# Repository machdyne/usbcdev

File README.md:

# USBCDEV Pmod™ Compatible Module

This is a simple USB-C module for developing certain USB-C devices directly in FPGA gateware. Note that it’s not possible to precisely meet the USB specs with this PMOD but it might be close enough for your purposes, please check the schematics and layout.

This repo contains PCB layouts, schematics and pinouts.

Find more information on the [product page](https://machdyne.com/product/usbcdev-pmod/).

## Pinout

| Pin | Signal |
| --- | ------ |
| 1 | USB\_DP |
| 2 | USB\_DN |
| 3 | USB\_DP\_PU |
| 4 | USB\_DN\_PU |
| 5 | GND |
| 6 | 3V3 |

## License

The contents of this repo are released under the [Lone Dynamics Open License](LICENSE.md) with the following exceptions:

- The KiCad design files contain parts of the [kicad-pmod](https://github.com/mithro/kicad-pmod) library which is released under the [Apache License, Version 2.0](https://www.apache.org/licenses/LICENSE-2.0.html).

- The KiCad design files may contain symbols and footprints released under other licenses; please contact us if we've failed to give proper attribution.

Note: You can use these designs for commercial purposes but we ask that instead of producing exact clones, that you either replace our trademarks and logos with your own or add your own next to ours.

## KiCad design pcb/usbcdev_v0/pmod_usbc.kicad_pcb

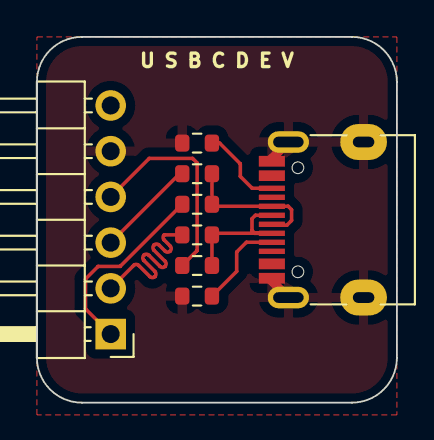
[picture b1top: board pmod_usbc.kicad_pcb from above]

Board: 2 copper layers, 20.0 x 20.3 mm, 8 parts (0 on the bottom side), 9 nets.

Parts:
J1: TYPE-C-31-M-12-FIXED; USB_C_Receptacle_HRO_TYPE-C-31-M-12-BIG-PADS
PMOD1: PMOD-Device-x1-Type-1-GPIO; PinHeader_1x06_P2.54mm_Horizontal
R1, R3: 5K1; R_0603_1608Metric
R2, R4: 22R; R_0603_1608Metric
R5, R6: 1K5; R_0603_1608Metric

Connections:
/USBC_DN: J1.A7 (DN1), J1.B7 (DN2), R2.1, R5.1
/USBC_DP: J1.A6 (DP1), J1.B6 (DP2), R4.1, R6.1
/USB_DN: PMOD1.2 (IO1), R2.2
/USB_DN_PU: PMOD1.4 (IO3), R5.2
/USB_DP: PMOD1.1 (IO0), R4.2
/USB_DP_PU: PMOD1.3 (IO2), R6.2
GND: J1.A1 (GND), J1.A12 (GND), J1.B1 (GND), J1.B12 (GND), J1.S1 (SHIELD), PMOD1.5 (GND), R1.2, R3.2
unnamed: J1.A5 (CC1), R3.1
unnamed: J1.B5 (CC2), R1.1
